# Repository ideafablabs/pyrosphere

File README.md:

# pyrosphere
Pyro Sphere hardware and software

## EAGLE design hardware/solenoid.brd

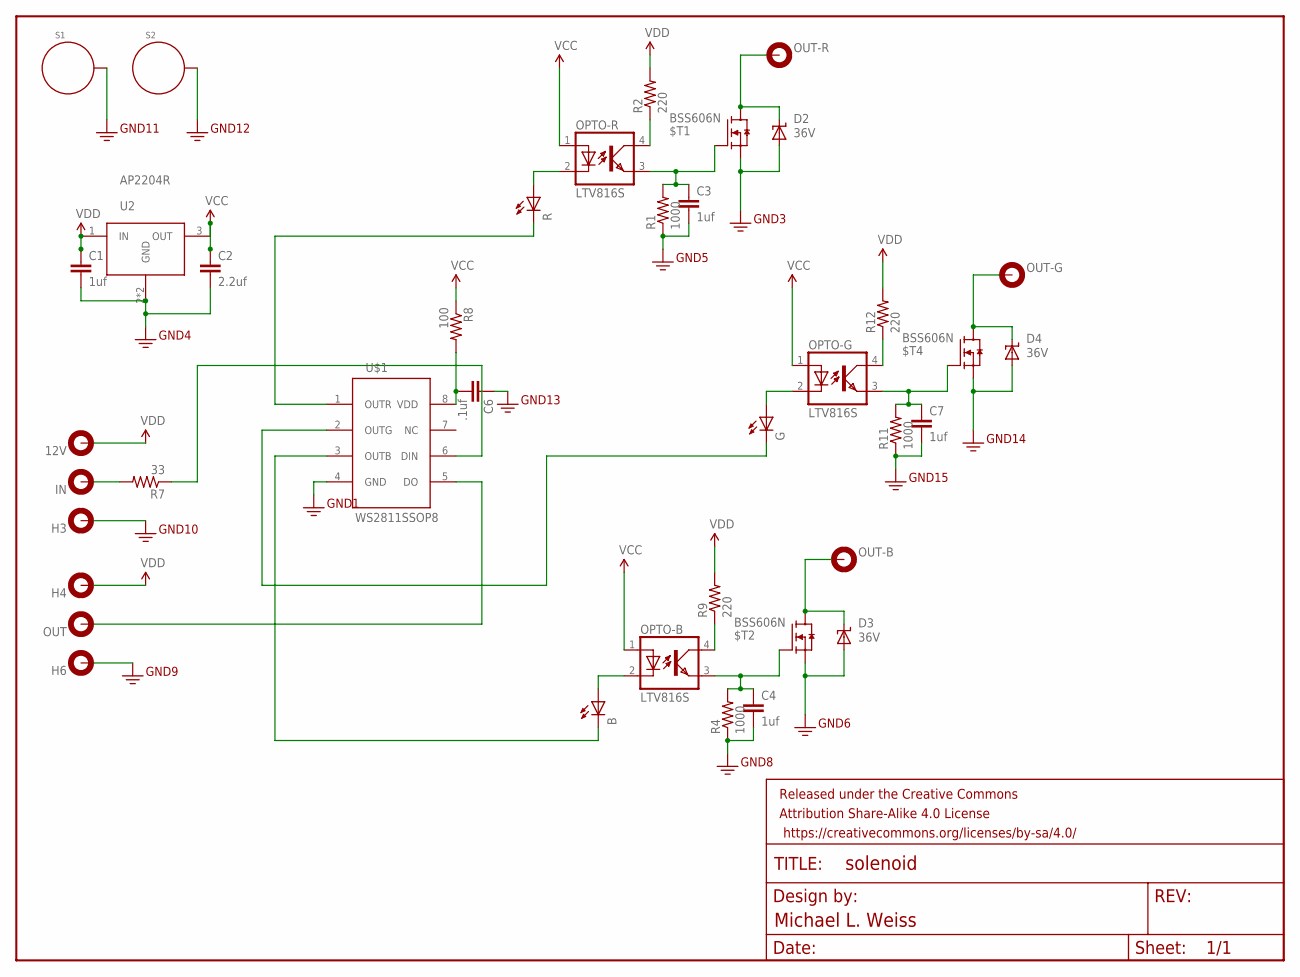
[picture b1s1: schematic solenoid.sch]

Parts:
12V: MOUNT-PAD-ROUND2.8; 2,8-PAD
$T1, $T2, $T4: BSS606N; SOT89R
B: LEDCHIPLED_0805; CHIPLED_0805
C1, C3, C4, C7: 1uf; 0805
C2: 2.2uf; 0805
C6: .1uf; 0805
D2, D3, D4: 36V; SMBJ
FRAME1: FRAME-LETTERNO_PACKAGE; DUMMY
G: LEDCHIPLED_0805; CHIPLED_0805
H3, H4, H6: MOUNT-PAD-ROUND2.8; 2,8-PAD
IN: MOUNT-PAD-ROUND2.8; 2,8-PAD
OPTO-B: LTV816S; DIL4-SMD
OPTO-G: LTV816S; DIL4-SMD
OPTO-R: LTV816S; DIL4-SMD
OUT: MOUNT-PAD-ROUND2.8; 2,8-PAD
OUT-B: MOUNT-PAD-ROUND2.8; 2,8-PAD
OUT-G: MOUNT-PAD-ROUND2.8; 2,8-PAD
OUT-R: MOUNT-PAD-ROUND2.8; 2,8-PAD
R: LEDCHIPLED_0805; CHIPLED_0805
R1, R4, R11: 1000; 0805
R2, R9, R12: 220; 0805
R7: 33; 0805
R8: 100; 0805
S1, S2: STANDOFF_ELECTRICAL; STANDOFF-ELECTRICAL
U2: AP2204R; SOT89R
U$1: WS2811SSOP8; SOIC8_150MIL

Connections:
GND: $T1.3 (S), $T2.3 (S), $T4.3 (S), C1.2, C2.2, C3.2, C4.2, C6.1, C7.2, D2.A, D3.A, D4.A, H3.B2,8, H6.B2,8, R1.1, R4.1, R11.1, S1.P1, S2.P1, U2.2 (GND), U2.4 (GND), U$1.4 (GND)
IN: IN.B2,8, R7.2
unnamed: B.C, U$1.3 (OUTB)
unnamed: G.C, U$1.2 (OUTG)
unnamed: $T1.1 (G), C3.1, OPTO-R.3 (EMIT), R1.2
unnamed: OPTO-R.4 (COL), R2.1
unnamed: OPTO-R.2 (C), R.A
unnamed: R.C, U$1.1 (OUTR)
unnamed: $T2.1 (G), C4.1, OPTO-B.3 (EMIT), R4.2
unnamed: R7.1, U$1.6 (DIN)
unnamed: OPTO-B.4 (COL), R9.1
unnamed: B.A, OPTO-B.2 (C)
unnamed: $T4.1 (G), C7.1, OPTO-G.3 (EMIT), R11.2
unnamed: OPTO-G.4 (COL), R12.1
unnamed: G.A, OPTO-G.2 (C)
unnamed: C6.2, R8.2, U$1.8 (VDD)
OUT: OUT.B2,8, U$1.5 (DO)
OUT-B: $T2.2 (D), $T2.4 (D), D3.C, OUT-B.B2,8
OUT-G: $T4.2 (D), $T4.4 (D), D4.C, OUT-G.B2,8
OUT-R: $T1.2 (D), $T1.4 (D), D2.C, OUT-R.B2,8
VCC: C2.1, OPTO-B.1 (A), OPTO-G.1 (A), OPTO-R.1 (A), R8.1, U2.3 (OUT)
VDD: 12V.B2,8, C1.1, H4.B2,8, R2.2, R9.2, R12.2, U2.1 (IN)

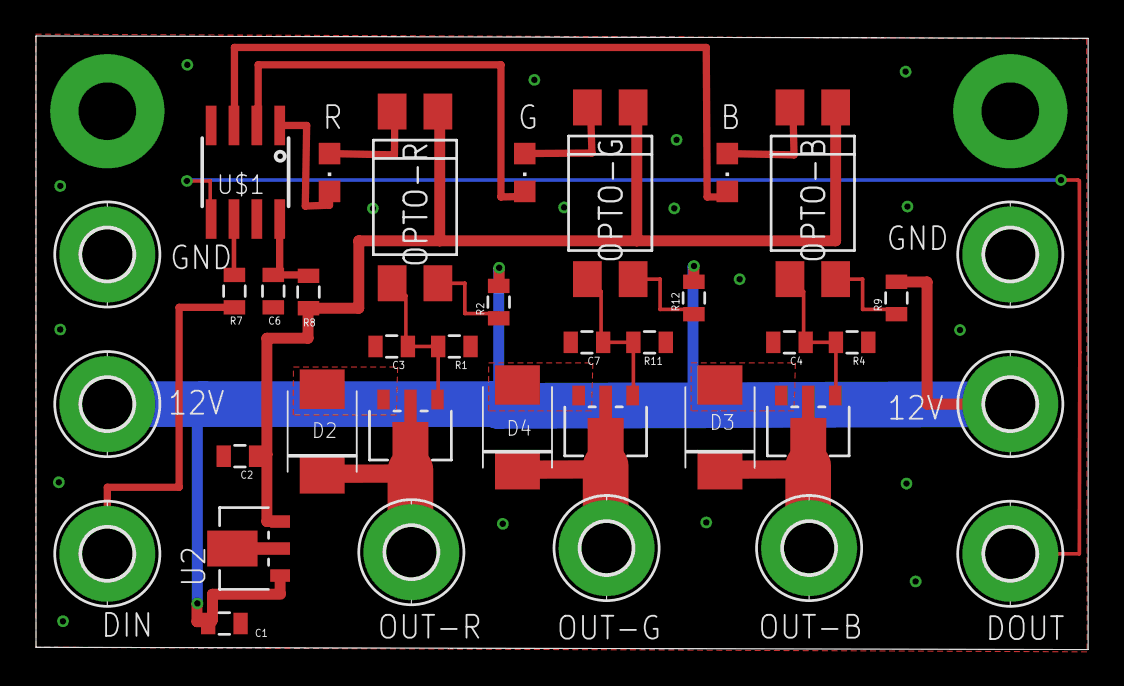
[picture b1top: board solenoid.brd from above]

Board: 2 copper layers, 58.5 x 34.1 mm, 41 parts (0 on the bottom side), 22 nets.

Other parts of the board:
U$2: IFL-LOGO

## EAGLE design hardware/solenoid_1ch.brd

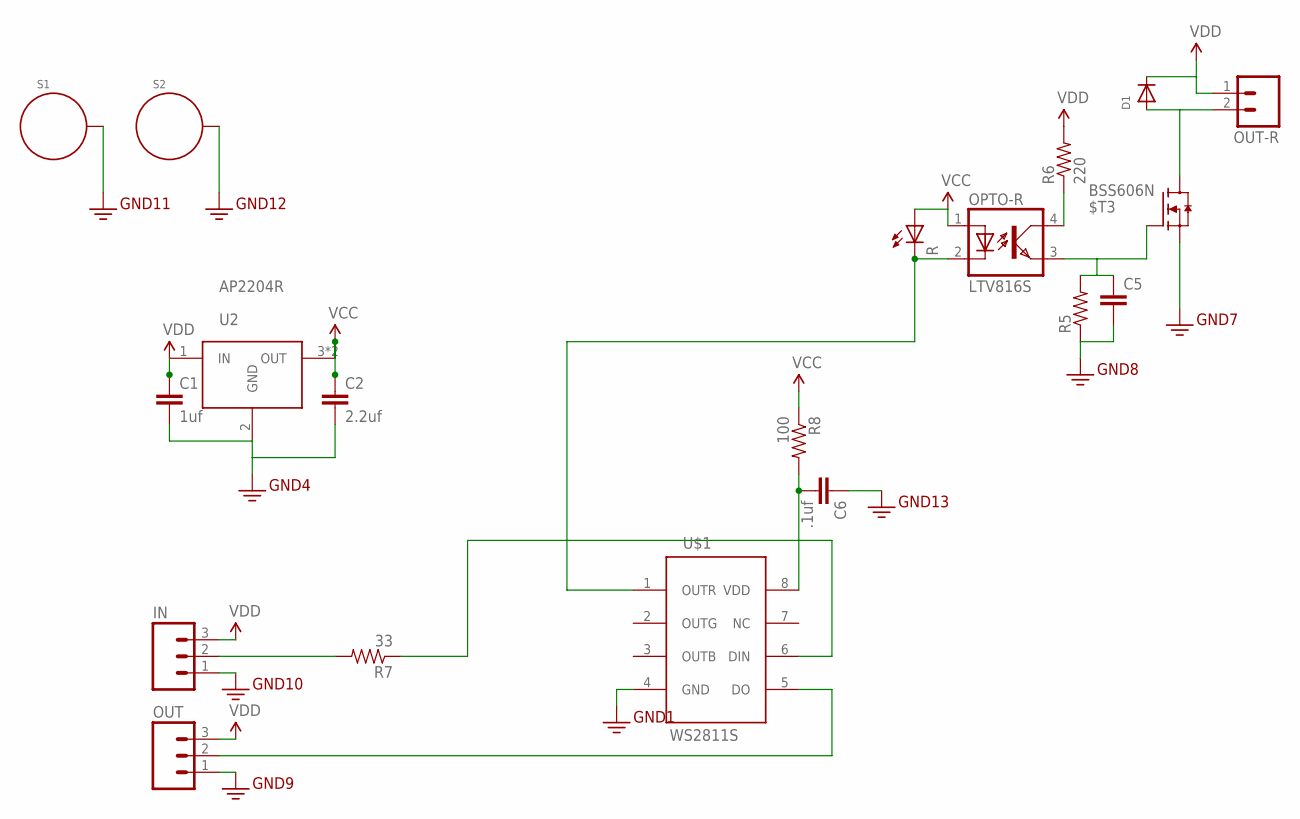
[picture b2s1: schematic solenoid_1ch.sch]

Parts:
$T3: BSS606N; SOT89R
C1: 1uf; 0805
C2: 2.2uf; 0805
C5: CAP0805; 0805
C6: .1uf; 0805
D1: DIODESOD-123; SOD-123
IN: M031X03_NO_SILK; 1X03_NO_SILK
OPTO-R: LTV816S; SMD4
OUT: M031X03_NO_SILK; 1X03_NO_SILK
OUT-R: M02PTH; 1X02
R: LEDCHIPLED_0805; CHIPLED_0805
R5: RESISTOR0805-RES; 0805
R6: 220; 0805
R7: 33; 0805
R8: 100; 0805
S1, S2: STANDOFF_ELECTRICAL; STANDOFF-ELECTRICAL
U2: AP2204R; SOT89R
U$1: WS2811S; MSOP8

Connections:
GND: $T3.1 (S), C1.2, C2.2, C5.2, C6.1, IN.1, OUT.1, R5.1, S1.P1, S2.P1, U2.2 (GND), U$1.4 (GND)
unnamed: OPTO-R.2 (C), R.C, U$1.1 (OUTR)
unnamed: $T3.2 (G), C5.1, OPTO-R.3 (EMIT), R5.2
unnamed: OPTO-R.4 (COL), R6.1
unnamed: $T3.3 (D), $T3.4 (D), D1.A, OUT-R.2
unnamed: R7.1, U$1.6 (DIN)
unnamed: OUT.2, U$1.5 (DO)
unnamed: IN.2, R7.2
unnamed: C6.2, R8.2, U$1.8 (VDD)
VCC: C2.1, OPTO-R.1 (A), R.A, R8.1, U2.3 (OUT), U2.4 (OUT)
VDD: C1.1, D1.C, IN.3, OUT.3, OUT-R.1, R6.2, U2.1 (IN)

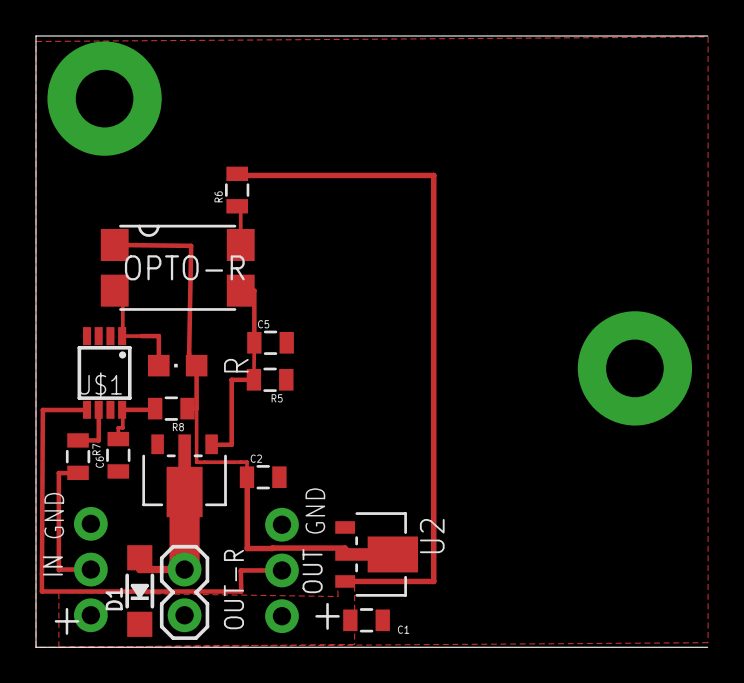
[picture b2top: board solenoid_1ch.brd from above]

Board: 2 copper layers, 37.3 x 34.0 mm, 19 parts (0 on the bottom side), 11 nets.

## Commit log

2017-03-29 First revision (really V0.1)
2017-03-29 PDF of schematic
2017-04-04 Fixed GND via(s) name
2017-04-04 Put in values for the low pass resistors and caps, This is an estimate.
2017-04-04 Added protection diodes
2017-05-18 Changed to TSDs instead of flyback diodes and increased the solder holw sizes
2017-05-26 Fixed problem with reguslator having wrong footprint.
2017-06-04 Changed from 470nf to 1uf for the filter cap now I get no chatter on my solenoids when I have the level at 127.

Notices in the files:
parts and their libraries:
SparkFun-Capacitors: Licensing: Creative Commons ShareAlike 4.0 International - https://creativecommons.org/licenses/by-sa/4.0
SparkFun-Aesthetics: Released under the Creative Commons Attribution Share-Alike 4.0 License
SparkFun-Aesthetics: https://creativecommons.org/licenses/by-sa/4.0
